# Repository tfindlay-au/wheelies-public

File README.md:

# wheelies-public
Code resources for the wheelie project - track your wheelie data and improve.

## Data Collection Rig

### Hardware

It doesn’t get much slicker than this. The hardware comprises:
* 1 bike (A)
* 1 smartphone (B)
* 1 roll duct tape (C)

Using a generous amount of duct tape (C), affix the phone (B) to the top tube of the bike (A) near the head. 

Pro-tips:
1. First, open the SensorLog app (see below)
2. Position the duct tape so that (i) the “Device Motion” traces are visible for a cool cockpit display and (ii) it’s easy to press the record button at bottom left
3. For nocturnal wheelies, a front light pointing down illuminates the ground in front when the wheel is up in the air
4. A bell may be required by law for riding local streets in Australia

### Software

The software comprises:
* [SensorLog](http://sensorlog.berndthomas.net/) app for iOS (or consider AndroSensor for Android)
* Google Drive account and app installed on the phone
* [Process Sensor Data](process_sensor_data.ipynb) notebook to run on [Colaboratory](https://colab.research.google.com/) 

To configure the data logged:
* Set SensorLog to log to a file on the device 
* Select CSV format
* Set desired logging frequency. I have settled on 10Hz, but will review in future.
* Log the following sensors: minimum: “Device Motion”; recommended, add: Accelerometer, Core Location, Gyro, Heading, Magnetometer (or Android equivalents)

After each session, the recorded data can be uploaded to a Google Drive folder as a CSV file.

## Data Processing Notebook

See [Process Sensor Data](process_sensor_data.ipynb) notebook to run on [Colaboratory](https://colab.research.google.com/)

## Future ideas
* Consider calculating Time-Of-Flight (ToF) for speed of movement.
** Best speed for wheelie ?
** Entry vs Exit speed
* Consider calculating "steadiness" of other axis - is the wheelie straight ?

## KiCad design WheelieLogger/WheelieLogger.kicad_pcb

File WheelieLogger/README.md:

## Objective
This folder contains a schematic and PCB to construct a device
that will capture movement from a sensor.

This project will evolve over time, I will attempt to describe time
as phases of development.

### Phase 1
Design a PCB based off the Serpente R2 by Arturo182. The SAMD21 processor
is low power and simple to use and has Circuit Python available.

The Serpente project also provides open source schematic and PCB to get started
with.

The result of this phase is to have a working PCB produced with the addition of
a built-in motion sensor.

### Phase 2
Expanding on the learnings of Phase1, this will attempt to resolve
the issues. Namely:

1. Schematic fault with capacitor C9 which stops the board getting power without hacking away at it.
2. The omission of a LiPo charging circuit is an impediment to the devices use.
3. The on/off switch for the battery operation incorrectly spec'd as through-hole(THT) rather than Surface mount (SMD)

### Phase 3
With a usable device from phase 2, we now expand on its functionality
to provide feedback via LED's / Screen / Buzzer

## Getting started
The PCB is designed in KiCad and is tied to a nightly build. You must use this same version to open these files.

## Getting it made
To use an external service you will need to export a Gerber bundle and a bill of materials (BOM) file.

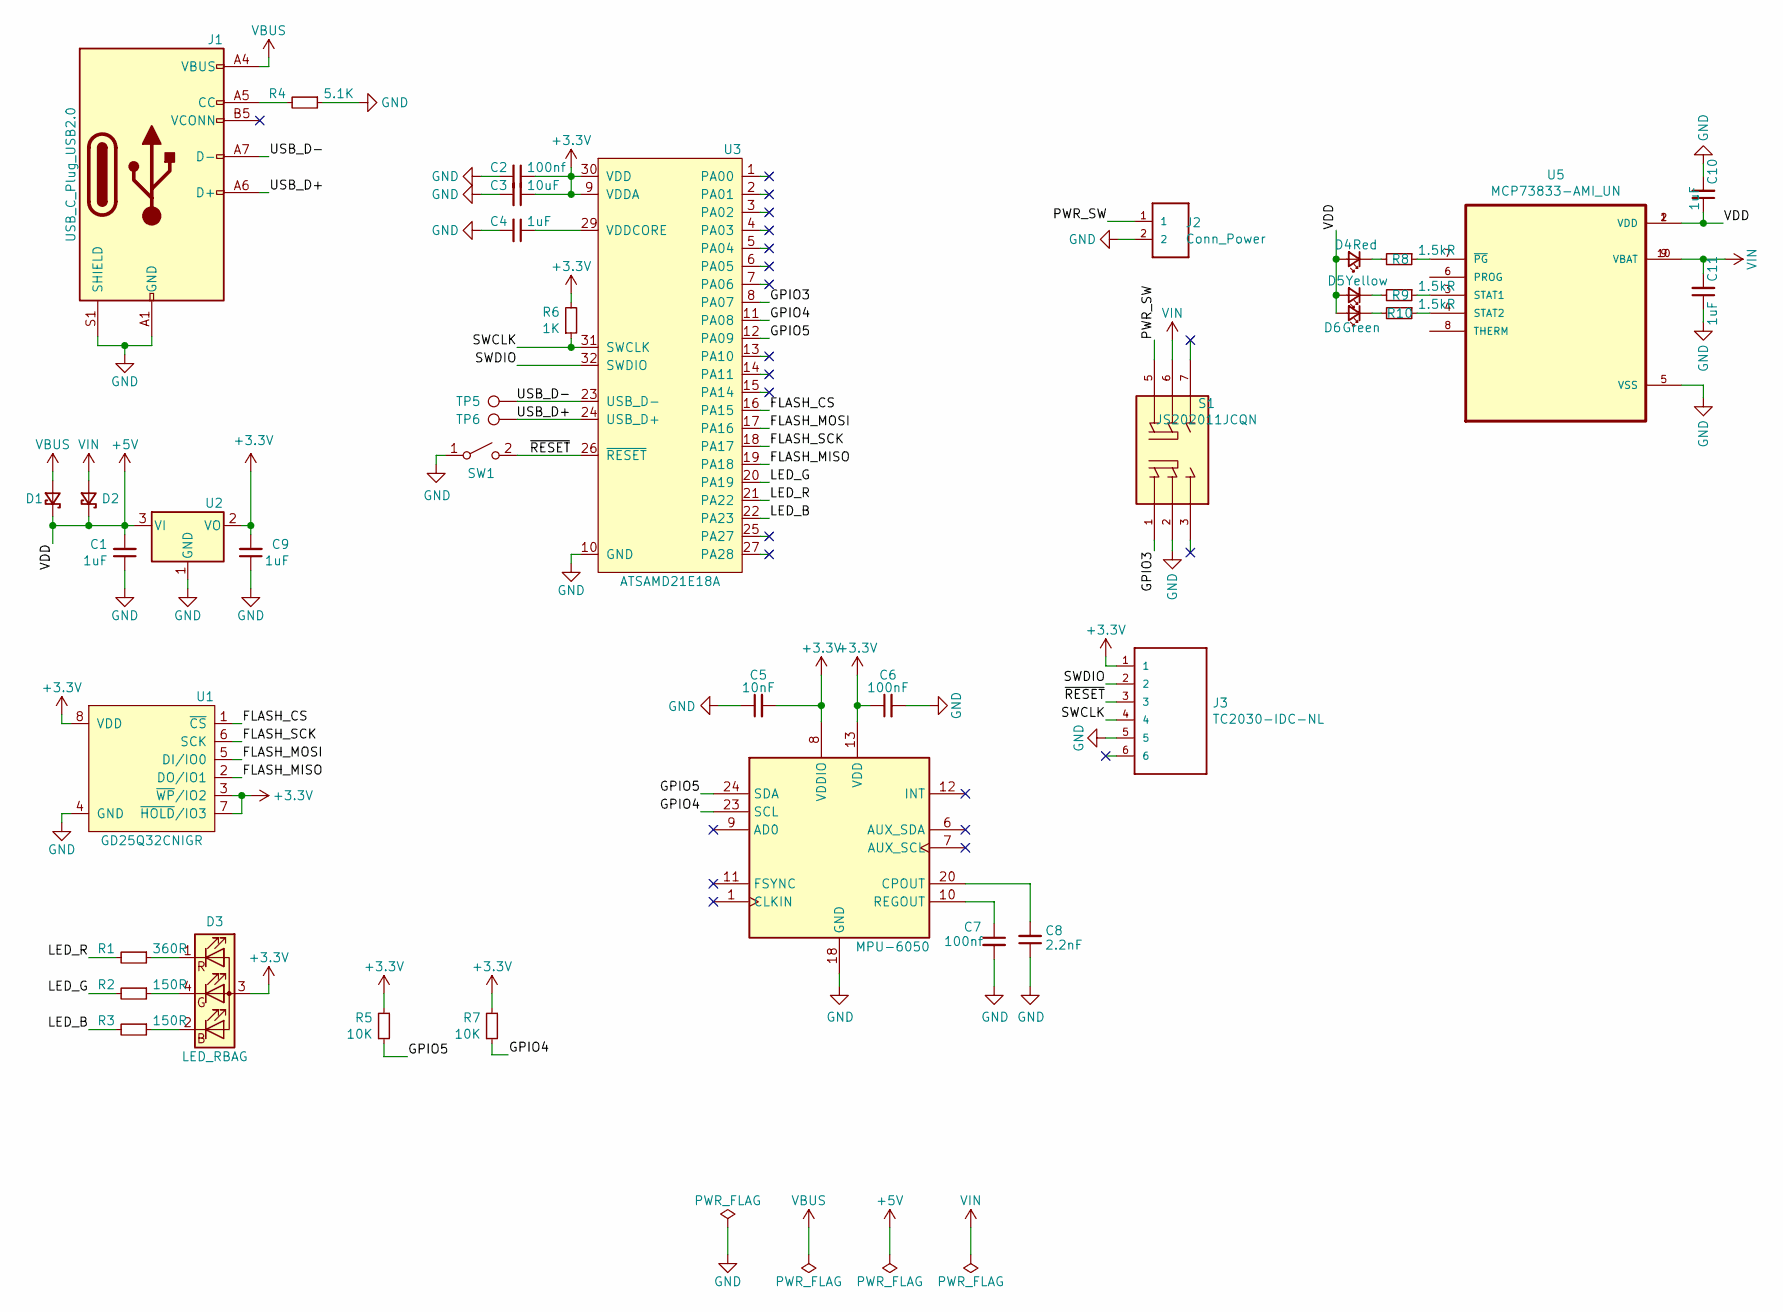
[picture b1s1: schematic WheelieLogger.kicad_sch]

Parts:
C1, C4, C9, C10, C11: 1uF; C_0402_1005Metric; LCSC C115046
C2, C7: 100nf; C_0402_1005Metric; LCSC C541406
C3: 10uF; C_0402_1005Metric; LCSC C105884
C5: 10nF; C_0402_1005Metric; LCSC C541370
C6: 100nF; C_0402_1005Metric; LCSC C541406
C8: 2.2nF; C_0402_1005Metric; LCSC C106861
D1, D2: D_Schottky_Small; D_SOD-323_HandSoldering; LCSC C114023
D3: LED_RBAG; LED_Cree-PLCC4_2x2mm_CW; LCSC C727904
D4: Red; LED_0402_1005Metric
D5: Yellow; LED_0402_1005Metric
D6: Green; LED_0402_1005Metric
J1: USB_C_Plug_USB2.0; USB_C_Receptacle_XKB_U262-16XN-4BVC11; LCSC C319148
J2: Conn_Power; JST_PH_B2B-PH-K_1x02_P2.00mm_Vertical; LCSC C131337
J3: TC2030-IDC-NL; Tag-Connect_TC2030-IDC-NL
R1: 360R; R_0402_1005Metric
R2, R3: 150R; R_0402_1005Metric
R4: 5.1K; R_0402_1005Metric
R5, R7: 10K; R_0402_1005Metric
R6: 1K; R_0402_1005Metric
R8, R9, R10: 1.5kR; R_0402_1005Metric
S1: JS202011JCQN; SW_JS202011JCQN
SW1: SW_RESET; SW_SPST_B3U-1000P-B; LCSC C231330
TP5: TP_USB_D-; TestPoint_Pad_D1.0mm
TP6: TP_USB_D+; TestPoint_Pad_D1.0mm
U1: GD25Q32CNIGR; USON-8_3x4mm_P0.8mm; LCSC C395491
U2: MCP1700-3302E_SOT23; SOT-23; LCSC C39051
U3: ATSAMD21E18A; QFN-32-1EP_5x5mm_P0.5mm_EP3.6x3.6mm; LCSC C220692
U4: MPU-6050; InvenSense_QFN-24_4x4mm_P0.5mm
U5: MCP73833-AMI_UN; SON50P300X300X100-11N

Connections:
+5V: C1.2, C10.1, D1.1 (K), D2.1 (K), D4.2 (A), D5.2 (A), D6.2 (A), U2.3 (VI), U5.1 (VDD), U5.2 (VDD)
/FLASH_CS: U1.1 (~CS~), U3.16 (PA15)
/FLASH_MISO: U1.2 (DO/IO1), U3.19 (PA18)
/FLASH_MOSI: U1.5 (DI/IO0), U3.17 (PA16)
/FLASH_SCK: U1.6 (SCK), U3.18 (PA17)
/GPIO3: S1.1, U3.8 (PA07)
/GPIO4: R7.1, U3.11 (PA08), U4.23 (SCL)
/GPIO5: R5.1, U3.12 (PA09), U4.24 (SDA)
/LED_B: R3.2, U3.22 (PA23)
/LED_G: R2.2, U3.20 (PA19)
/LED_R: R1.2, U3.21 (PA22)
/PWR_SW: J2.1, S1.5
/SWCLK: J3.4, R6.1, U3.31 (SWCLK)
/SWDIO: J3.2, U3.32 (SWDIO)
/USB_D+: J1.A6 (D+), TP6.1, U3.24 (USB_D+)
/USB_D-: J1.A7 (D-), TP5.1, U3.23 (USB_D-)
/~RESET~: J3.3, SW1.2 (B), U3.26 (~RESET~)
GND: C1.1, C2.2, C3.2, C4.2, C5.1, C6.2, C7.2, C8.1, C9.1, C10.2, C11.1, J1.A1 (GND), J1.A12 (GND), J1.B1 (GND), J1.B12 (GND), J1.S1 (SHIELD), J2.2, J3.5, R4.1, S1.2, SW1.1 (A), U1.4 (GND), U2.1 (GND), U3.10 (GND), U3.28 (GND), U4.18 (GND), U5.5 (VSS)
unnamed: C4.1, U3.29 (VDDCORE)
unnamed: C7.1, U4.10 (REGOUT)
unnamed: C8.2, U4.20 (CPOUT)
unnamed: D3.1 (RK), R1.1
unnamed: D3.2 (BK), R3.1
unnamed: D3.4 (GK), R2.1
unnamed: D5.1 (K), R9.2
unnamed: D6.1 (K), R10.2
unnamed: J1.A5 (CC), R4.2
unnamed: R8.1, U5.7 (~PG)
unnamed: R9.1, U5.3 (STAT1)
unnamed: R10.1, U5.4 (STAT2)
VBUS: D1.2 (A), J1.A4 (VBUS), J1.A9 (VBUS), J1.B4 (VBUS), J1.B9 (VBUS)
VIN: C11.2, D2.2 (A), S1.6, U5.9 (VBAT), U5.10 (VBAT)

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
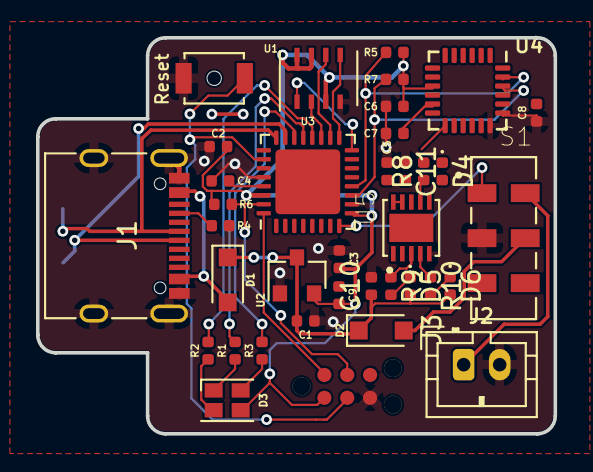
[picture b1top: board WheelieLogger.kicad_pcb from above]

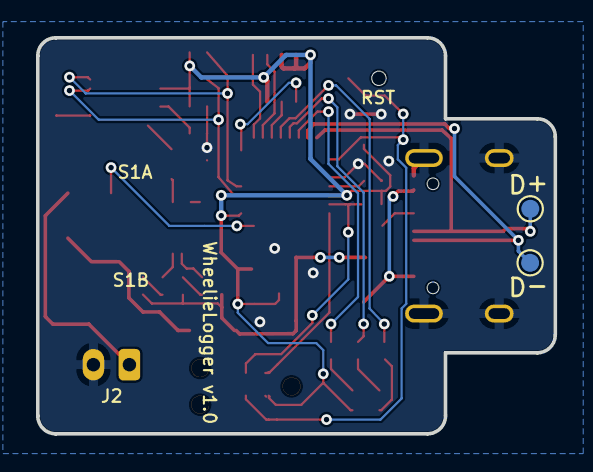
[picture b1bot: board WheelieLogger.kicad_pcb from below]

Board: 2 copper layers, 28.8 x 22.0 mm, 39 parts (2 on the bottom side), 33 nets.

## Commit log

2020-08-11 update gitignore
2020-08-11 data processing
2020-08-11 SensorLog config image
2020-08-11 update README instructions
2020-08-16 Draft of SerpenteR2 board instructions
2020-08-18 - Made the filesystem writing more robust - Added file size check - Reduced the delay in time.sleep() for more granular data - Improved some of the comments
2020-09-12 Draft of custom board based off Arturo182's Serpente R2
2020-09-24 1.Added 1uF cap to pin2 of the MCP1700 (U2) 2.Removed dip switches, replaced with DPDT slide switch as they should always operate together 3.Updated the JST-PH connector from an SMD to a through-hole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
2020-09-28 Rebuilt the tracks in the PCB Removed some test points
2020-09-30 Improved bottom layer GND mask Added part numbers for D1 and D2 Tidy up top and bottom silk screen layers
2020-10-04 Added J-link connector Moved the diodes to make room for it
2020-12-14 Updated to version 2
